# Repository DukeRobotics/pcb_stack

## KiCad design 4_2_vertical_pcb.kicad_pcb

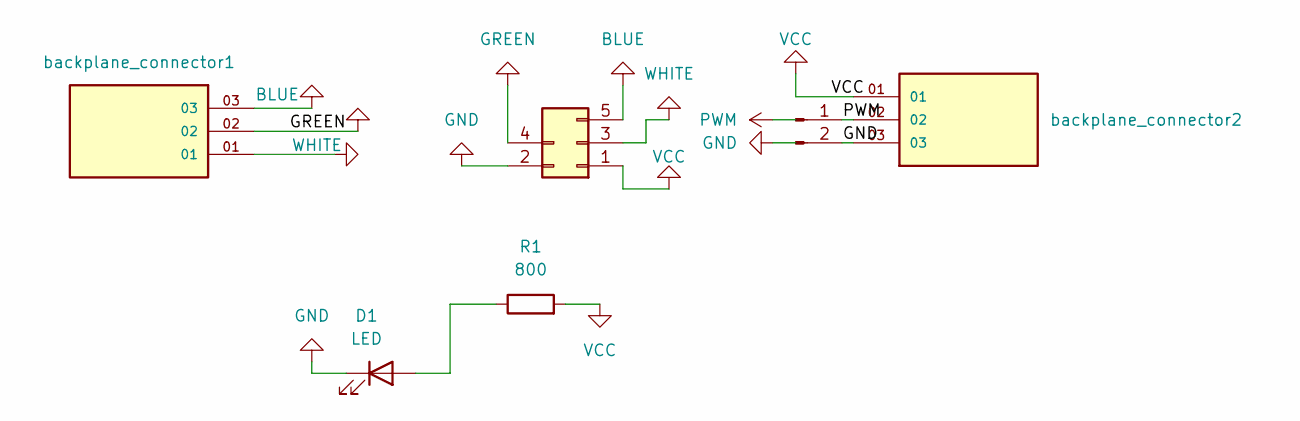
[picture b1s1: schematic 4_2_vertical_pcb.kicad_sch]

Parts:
D1: LED; LED_D5.0mm
Je1: ESC1; blue_escpcb (2)
PWM2: Conn_01x02_Pin; PinHeader_1x02_P2.54mm_Vertical
R1: 800; R_0805_2012Metric
backplane_connector1, backplane_connector2: IPBT-103-H1-T-S-GP; SAMTEC_IPBT-103-H1-T-S-GP; PARTREV R

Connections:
BLUE: Je1.5, backplane_connector1.03
GND: D1.1 (K), Je1.2, PWM2.2, backplane_connector2.03
GREEN: Je1.4, backplane_connector1.02
unnamed: D1.2 (A), R1.1
PWM: PWM2.1, backplane_connector2.02
VCC: Je1.1, R1.2, backplane_connector2.01
WHITE: Je1.3, backplane_connector1.01

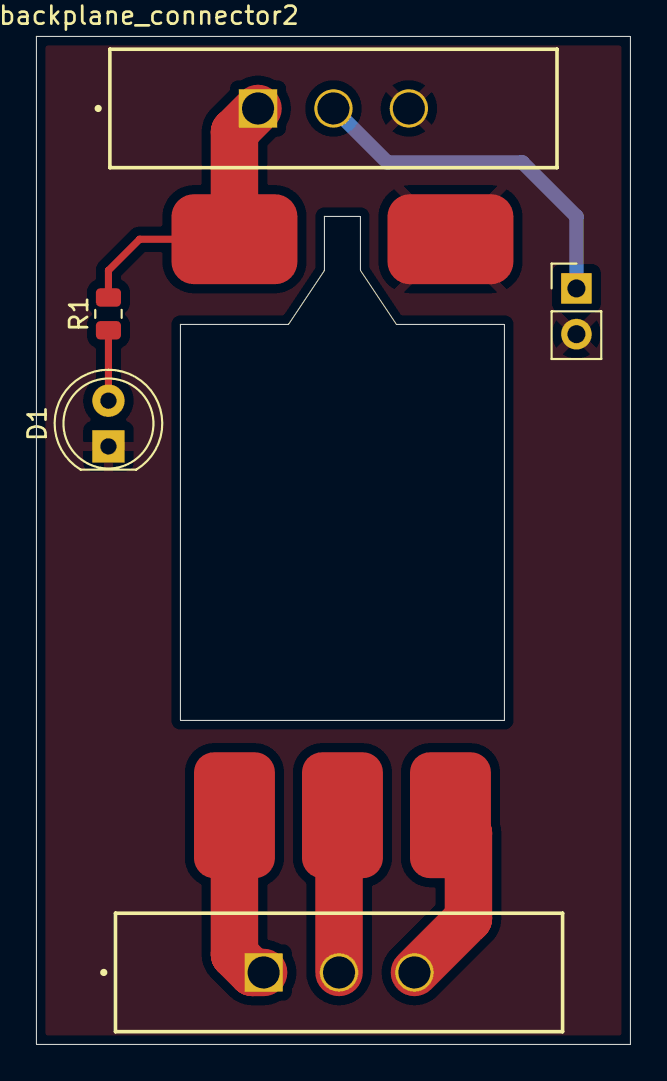
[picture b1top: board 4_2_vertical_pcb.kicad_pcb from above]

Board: 2 copper layers, 33.0 x 56.0 mm, 6 parts (0 on the bottom side), 7 nets.

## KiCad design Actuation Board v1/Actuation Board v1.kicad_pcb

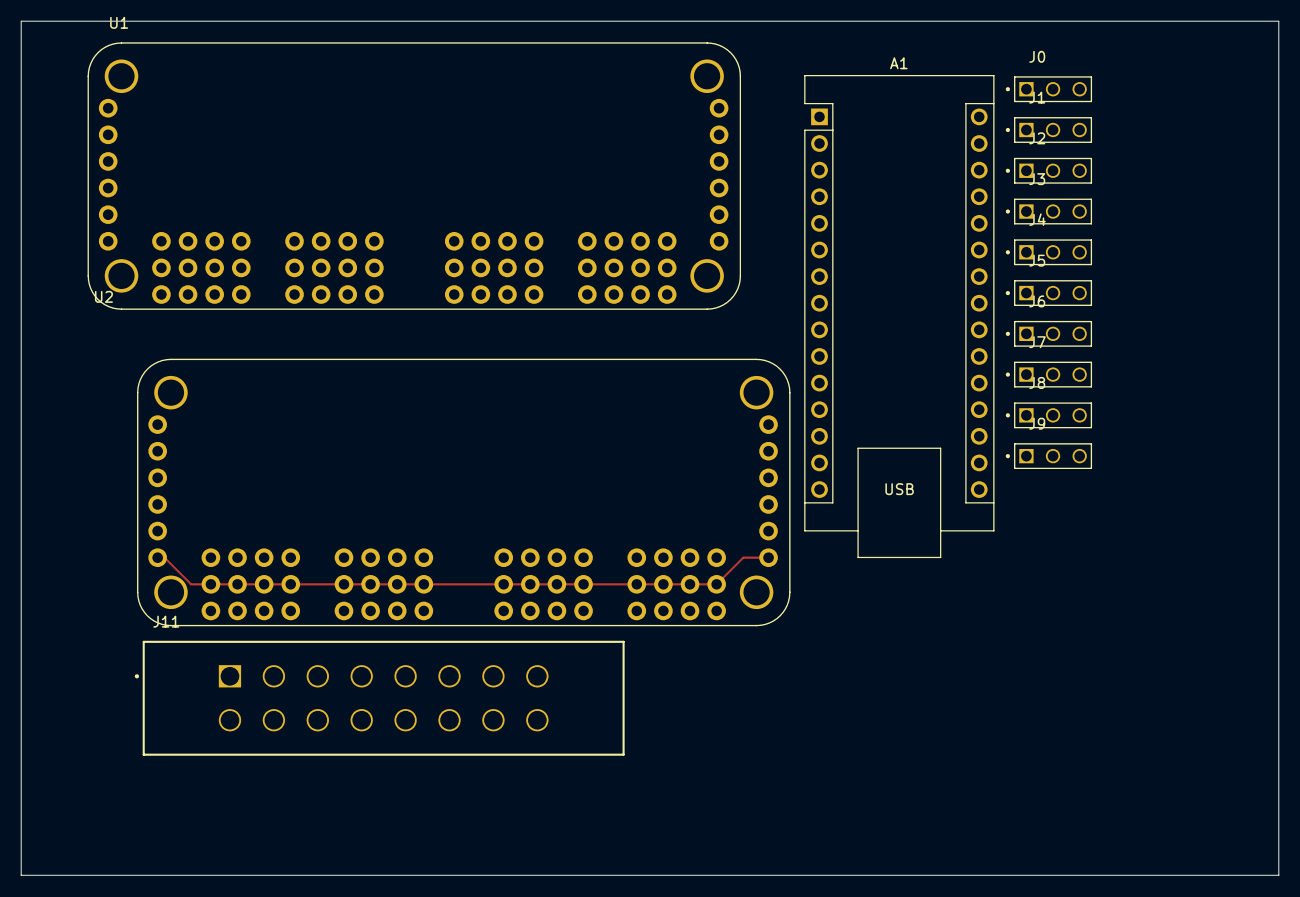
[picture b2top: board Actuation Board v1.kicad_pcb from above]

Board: 2 copper layers, 120.0 x 81.5 mm, 14 parts (0 on the bottom side), 27 nets.

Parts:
A1: Arduino_Nano_Every; Arduino_Nano
J0, J1, J2, J3, J4, J5, J6, J7: Servo_*; TE_644884-3
J8: Servo_power_0; TE_644884-3
J9: Servo_power_1; TE_644884-3
J11: IPBT-108-H1-T-D-GP; SAMTEC_IPBT-108-H1-T-D-GP
U1: PCA9685 THRUSTER MUX; MODULE_815
U2: PCA9685 SERVO MUX; MODULE_815

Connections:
+5V: J11.02, U1.VCC_1 (VCC), U1.VCC_2 (VCC), U2.VCC_1 (VCC), U2.VCC_2 (VCC)
/SCL: A1.24 (SCL/A5), U1.SCL_1 (SCL), U1.SCL_2 (SCL), U2.SCL_1 (SCL), U2.SCL_2 (SCL)
/SDA: A1.23 (SDA/A4), U1.SDA_1 (SDA), U1.SDA_2 (SDA), U2.SDA_1 (SDA), U2.SDA_2 (SDA)
/sc0: J0.3, U2.0 (PWM_0)
/sc1: J1.3, U2.1 (PWM_1)
/sc2: J2.3, U2.2 (PWM_2)
/sc3: J3.3, U2.3 (PWM_3)
/sc4: J4.3, U2.4 (PWM_4)
/sc5: J5.3, U2.5 (PWM_5)
/sc6: J6.3, U2.6 (PWM_6)
/sc7: J7.3, U2.7 (PWM_7)
/tc0: J11.03, U1.0 (PWM_0)
/tc1: J11.04, U1.1 (PWM_1)
/tc2: J11.05, U1.2 (PWM_2)
/tc3: J11.06, U1.3 (PWM_3)
/tc4: J11.11, U1.4 (PWM_4)
/tc5: J11.12, U1.5 (PWM_5)
/tc6: J11.13, U1.6 (PWM_6)
/tc7: J11.14, U1.7 (PWM_7)
GND: A1.4 (GND), A1.29 (GND), J0.1, J1.1, J2.1, J3.1, J4.1, J5.1, J6.1, J7.1, J11.01, J11.09, J11.15, U1.GND_1 (GND), U1.GND_2 (GND), U1.GND_3 (GND), U1.GND_4 (GND), U1.GND_5 (GND), U1.GND_6 (GND), U1.GND_7 (GND), U1.GND_8 (GND), U1.GND_9 (GND), U1.GND_10 (GND), U1.GND_11 (GND), U1.GND_12 (GND), U1.GND_13 (GND), U1.GND_14 (GND), U1.GND_15 (GND), U1.GND_16 (GND), U1.GND_17 (GND), U1.GND_18 (GND), U2.GND_1 (GND), U2.GND_2 (GND), U2.GND_3 (GND), U2.GND_4 (GND), U2.GND_5 (GND), U2.GND_6 (GND), U2.GND_7 (GND), U2.GND_8 (GND), U2.GND_9 (GND), U2.GND_10 (GND), U2.GND_11 (GND), U2.GND_12 (GND), U2.GND_13 (GND), U2.GND_14 (GND), U2.GND_15 (GND), U2.GND_16 (GND), U2.GND_17 (GND), U2.GND_18 (GND)
unnamed: J0.2, J1.2, J2.2, J3.2, J8.2
unnamed: J4.2, J5.2, J6.2, J7.2, J9.2
unnamed: U1.OE_1 (~OE), U1.OE_2 (~OE)
unnamed: U2.OE_1 (~OE), U2.OE_2 (~OE)
SP1: J8.1, J9.1, J11.08
SP2: J8.3, J9.3, J11.16
V+: U1.V+_1 (V+), U1.V+_2 (V+), U1.V+_3 (V+), U1.V+_4 (V+), U1.V+_5 (V+), U1.V+_6 (V+), U1.V+_7 (V+), U1.V+_8 (V+), U1.V+_9 (V+), U1.V+_10 (V+), U1.V+_11 (V+), U1.V+_12 (V+), U1.V+_13 (V+), U1.V+_14 (V+), U1.V+_15 (V+), U1.V+_16 (V+), U1.V+_17 (V+), U1.V+_18 (V+), U2.V+_1 (V+), U2.V+_2 (V+), U2.V+_3 (V+), U2.V+_4 (V+), U2.V+_5 (V+), U2.V+_6 (V+), U2.V+_7 (V+), U2.V+_8 (V+), U2.V+_9 (V+), U2.V+_10 (V+), U2.V+_11 (V+), U2.V+_12 (V+), U2.V+_13 (V+), U2.V+_14 (V+), U2.V+_15 (V+), U2.V+_16 (V+), U2.V+_17 (V+), U2.V+_18 (V+)

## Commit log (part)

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2026-02-07 actuation board schematic
2026-02-13 a few symbols added
